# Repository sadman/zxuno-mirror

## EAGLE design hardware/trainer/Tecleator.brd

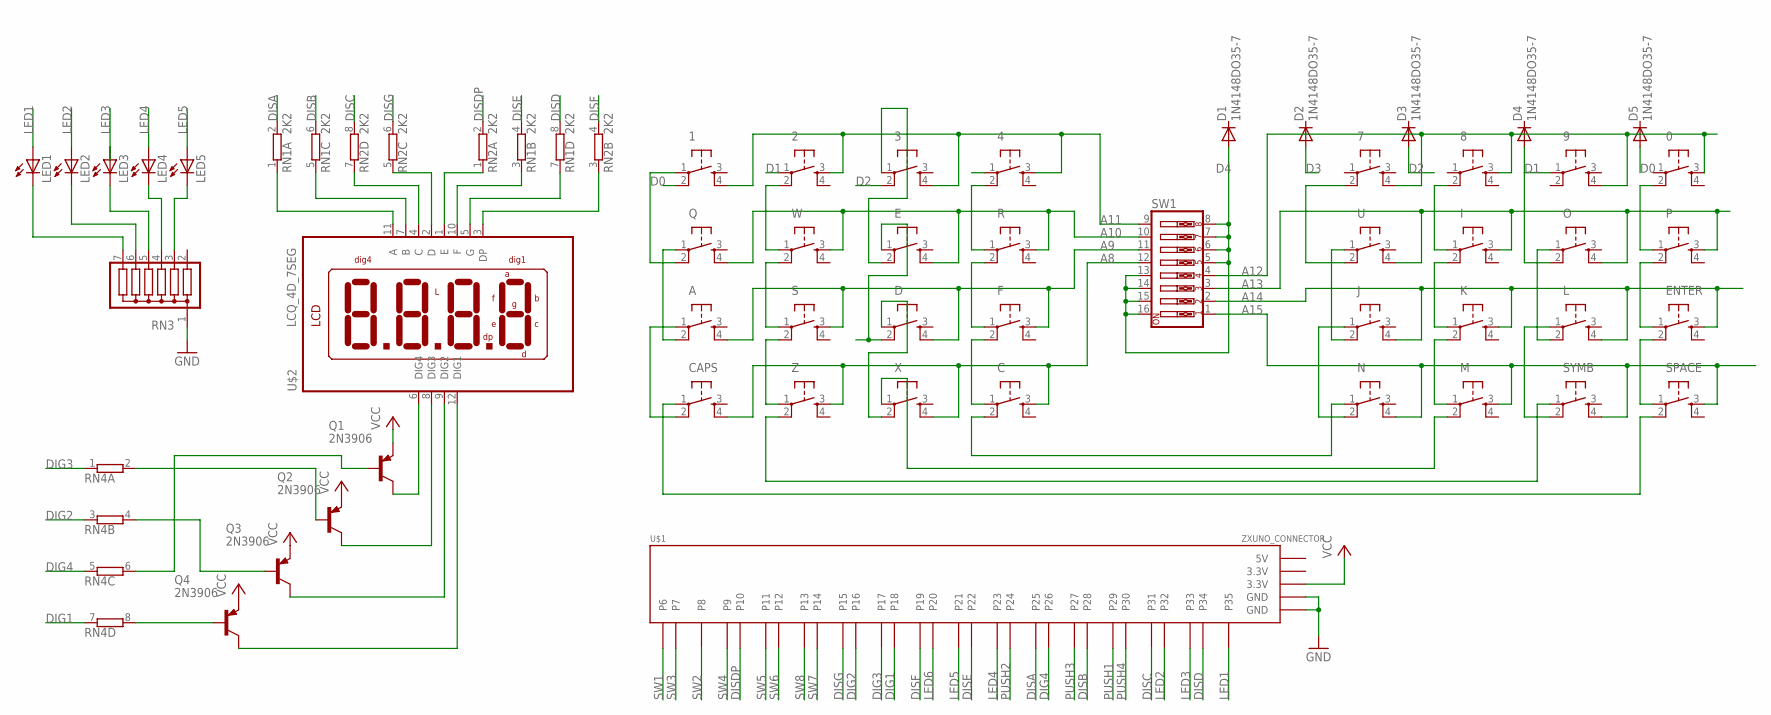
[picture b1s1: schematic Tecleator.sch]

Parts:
0, 1, 2, 3, 4, 7, 8, 9: DTS-6
A: DTS-6
C: DTS-6
CAPS: DTS-6
D: DTS-6
D1, D2, D3, D4, D5: 1N4148DO35-7; DO35-7
E: DTS-6
ENTER: DTS-6
F: DTS-6
I: DTS-6
J: DTS-6
K: DTS-6
L: DTS-6
LED1, LED2, LED3, LED4, LED5: LED3MM
M: DTS-6
N: DTS-6
O: DTS-6
P: DTS-6
Q: DTS-6
Q1, Q2, Q3, Q4: 2N3906; TO92
R: DTS-6
RN1, RN2: 2K2; SIL8
RN3: G06R; SIL7
RN4: E4R; SIL8
S: DTS-6
SPACE: DTS-6
SW1: SW_DIP-8; EDG-08
SYMB: DTS-6
U: DTS-6
U$1: ZXUNO_CONNECTOR
U$2: LCQ_4D_7SEG; LDQ_4D_7SEG
W: DTS-6
X: DTS-6
Z: DTS-6

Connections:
3.3V: U$1.3.3V@1 (3.3V)
5V: U$1.5V
A8: C.3, CAPS.4, SW1.12, X.4, Z.3
A9: A.4, D.4, F.3, S.3, SW1.11
A10: E.4, Q.4, R.3, SW1.10, W.3
A11: 1.4, 2.3, 3.4, 4.3, SW1.9
A12: 0.3, 7.4, 8.3, 9.4, SW1.4
A13: I.3, O.4, P.3, SW1.3, U.4
A14: ENTER.3, J.4, K.3, L.4, SW1.2
A15: M.3, N.4, SPACE.3, SW1.1, SYMB.4
D0: 1.2, D5.A
D1: 2.1, 9.1, D4.A, O.2
D2: 3.2, D3.A
D3: 4.1, D2.A
D4: D1.A, SW1.5, SW1.6, SW1.7, SW1.8, SW1.13, SW1.14, SW1.15, SW1.16
DIG1: RN4.7 (1), U$1.P18
DIG2: RN4.3 (1), U$1.P16
DIG3: RN4.1, U$1.P17
DIG4: RN4.5 (1), U$1.P26
DISA: RN1.2, U$1.P25
DISB: RN1.6 (2), U$1.P28
DISC: RN2.8 (2), U$1.P31
DISD: RN1.8 (2), U$1.P34
DISDP: RN2.2, U$1.P10
DISE: RN1.4 (2), U$1.P22
DISF: RN2.4 (2), U$1.P19
DISG: RN2.6 (2), U$1.P15
ELETE: M.2, X.1
GND: RN3.1, U$1.GND@1 (GND), U$1.GND@2 (GND)
LED1: LED1.A, U$1.P35
LED2: LED2.A, U$1.P32
LED3: LED3.A, U$1.P33
LED4: LED4.A, U$1.P23
LED5: LED5.A, U$1.P21
LED6: U$1.P20
unnamed: CAPS.1, SPACE.2
unnamed: 1.1, Q.2
unnamed: K.2, M.1
unnamed: Q1.1 (C), U$2.6 (DIG4)
unnamed: Q2.1 (C), U$2.8 (DIG3)
unnamed: Q3.1 (C), U$2.9 (DIG2)
unnamed: A.2, Q.1
unnamed: Q4.1 (C), U$2.12 (DIG1)
unnamed: A.1, CAPS.2
unnamed: 7.2, U.2
unnamed: 3.1, E.2
unnamed: S.1, W.2
unnamed: S.2, Z.1
unnamed: SYMB.1, Z.2
unnamed: Q4.2 (B), RN4.8 (2)
unnamed: RN1.1, U$2.11 (A)
unnamed: 4.2, R.1
unnamed: F.1, R.2
unnamed: C.1, F.2
unnamed: J.2, U.1
unnamed: J.1, N.2
unnamed: RN1.5 (1), U$2.7 (B)
unnamed: D.2, E.1
unnamed: 2.2, W.1
unnamed: RN2.7 (1), U$2.4 (C)
unnamed: RN2.5 (1), U$2.2 (D)
unnamed: RN2.1, U$2.1 (E)
unnamed: RN1.3 (1), U$2.10 (F)
unnamed: LED4.K (C), RN3.4
unnamed: LED5.K (C), RN3.3
unnamed: LED3.K (C), RN3.5
unnamed: LED2.K (C), RN3.6
unnamed: C.2, N.1
unnamed: L.1, SYMB.2
unnamed: LED1.K (C), RN3.7
unnamed: I.2, K.1
unnamed: 8.2, I.1
unnamed: L.2, O.1
unnamed: RN1.7 (1), U$2.5 (G)
unnamed: ENTER.2, SPACE.1
unnamed: ENTER.1, P.2
unnamed: 0.2, P.1
unnamed: RN2.3 (1), U$2.3 (DP)
unnamed: Q2.2 (B), RN4.2
unnamed: Q1.2 (B), RN4.6 (2)
unnamed: Q3.2 (B), RN4.4 (2)
unnamed: D.1, X.2
PUSH1: U$1.P29
PUSH2: U$1.P24
PUSH3: U$1.P27
PUSH4: U$1.P30
SW1: U$1.P6
SW2: U$1.P8
SW3: U$1.P7
SW4: U$1.P9
SW5: U$1.P11
SW6: U$1.P12
SW7: U$1.P14
SW8: U$1.P13
VCC: Q1.3 (E), Q2.3 (E), Q3.3 (E), Q4.3 (E), U$1.3.3V@2 (3.3V)

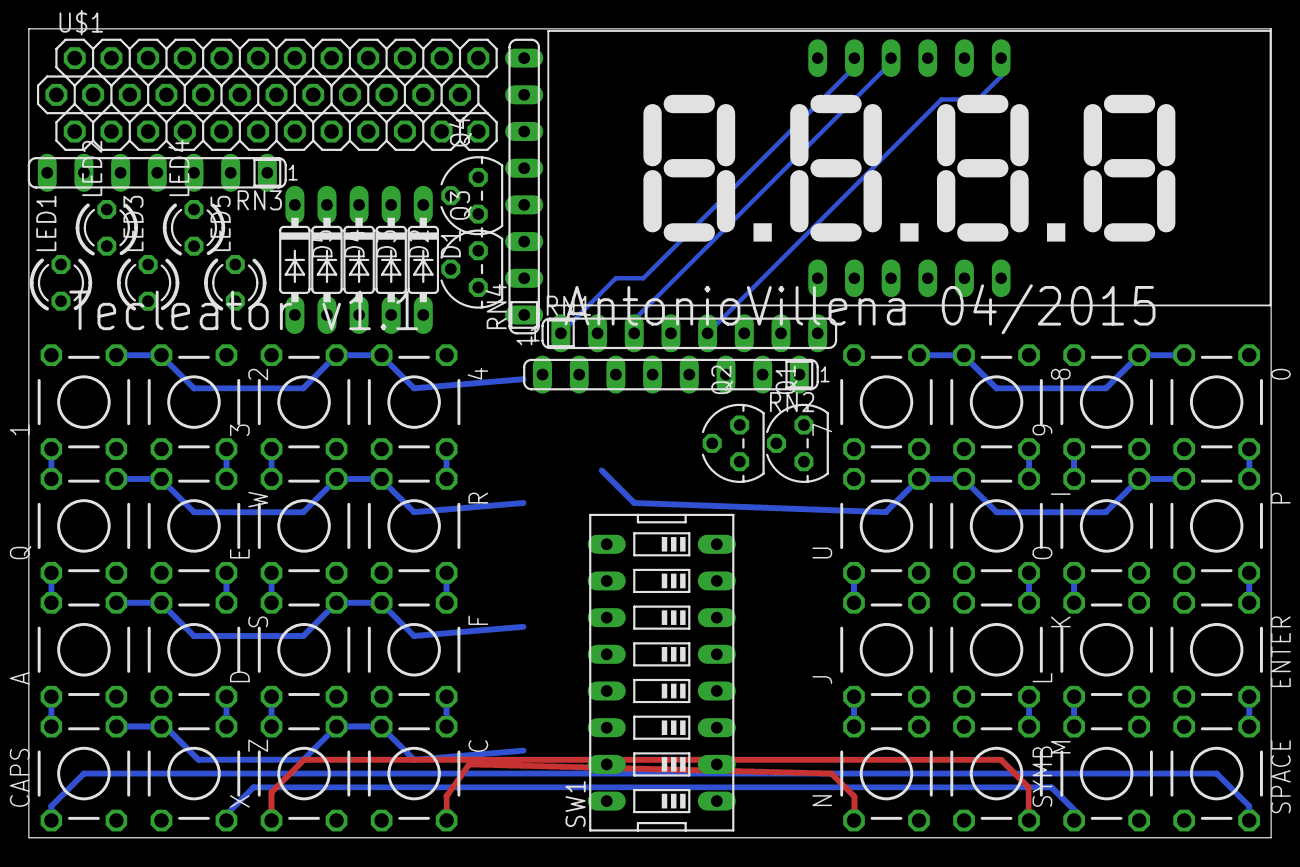
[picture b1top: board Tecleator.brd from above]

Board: 2 copper layers, 86.0 x 56.0 mm, 53 parts (0 on the bottom side), 80 nets.

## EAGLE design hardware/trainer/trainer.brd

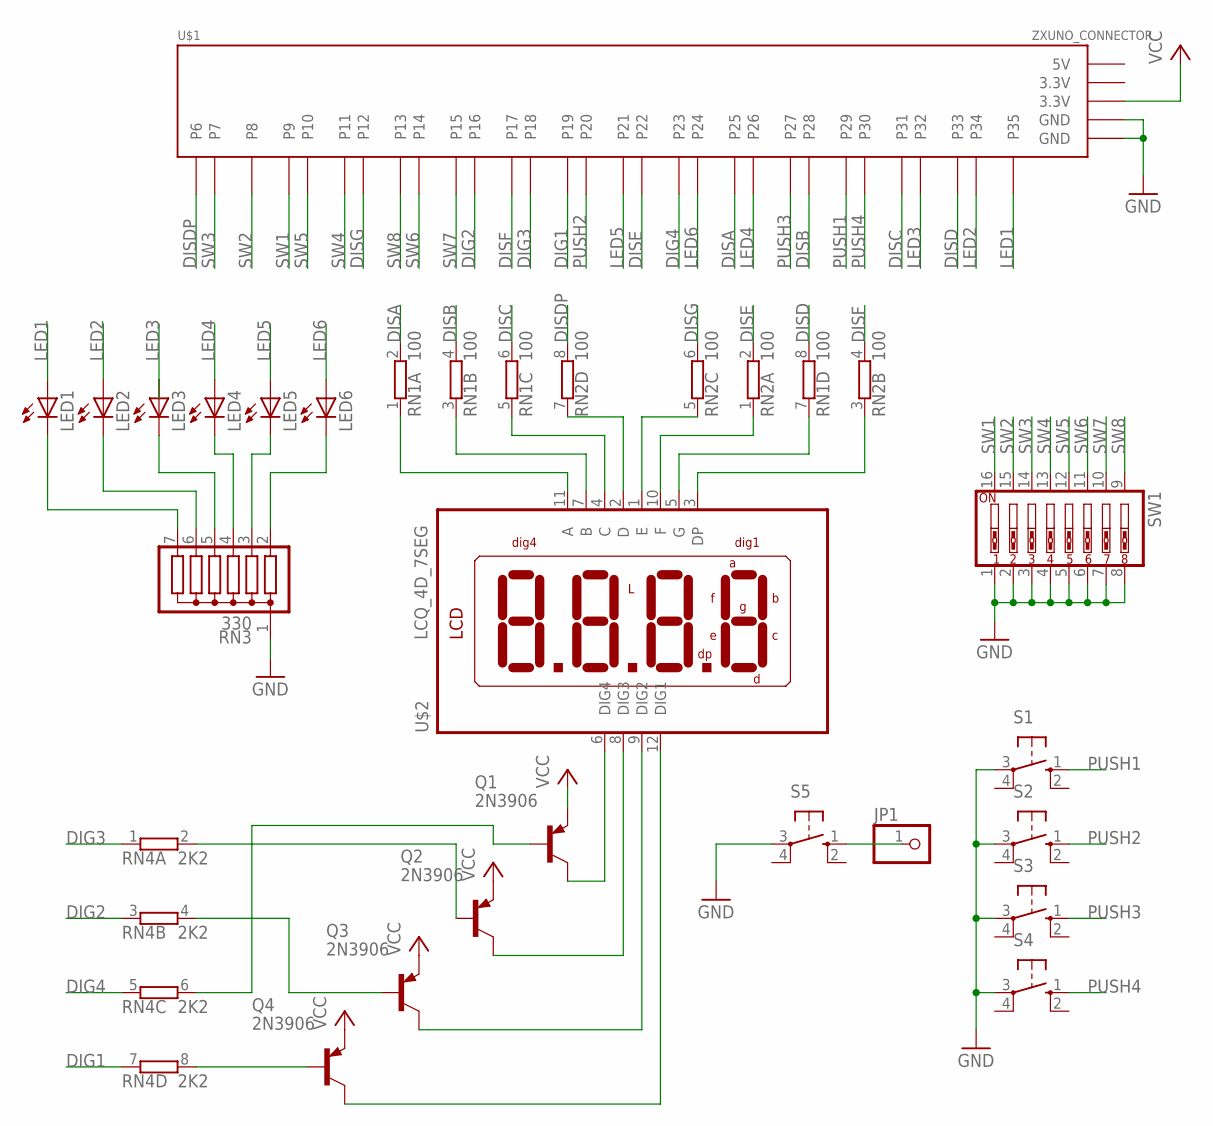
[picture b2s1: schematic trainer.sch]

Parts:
JP1: PINHD-1X1; 1X01
LED1, LED2, LED3, LED4, LED5, LED6: LED3MM
Q1, Q2, Q3, Q4: 2N3906; TO92
RN1, RN2: 100; SIL8
RN3: 330; SIL7
RN4: 2K2; SIL8
S1, S2, S3, S4, S5: 10-XX; B3F-10XX
SW1: SW_DIP-8; EDG-08
U$1: ZXUNO_CONNECTOR
U$2: LCQ_4D_7SEG; LDQ_4D_7SEG

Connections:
3.3V: U$1.3.3V@1 (3.3V)
5V: U$1.5V
DIG1: RN4.7 (1), U$1.P19
DIG2: RN4.3 (1), U$1.P16
DIG3: RN4.1, U$1.P18
DIG4: RN4.5 (1), U$1.P23
DISA: RN1.2, U$1.P25
DISB: RN1.4 (2), U$1.P28
DISC: RN1.6 (2), U$1.P31
DISD: RN1.8 (2), U$1.P33
DISDP: RN2.8 (2), U$1.P6
DISE: RN2.2, U$1.P22
DISF: RN2.4 (2), U$1.P17
DISG: RN2.6 (2), U$1.P12
GND: RN3.1, S1.3, S2.3, S3.3, S4.3, S5.3, SW1.1, SW1.2, SW1.3, SW1.4, SW1.5, SW1.6, SW1.7, SW1.8, U$1.GND@1 (GND), U$1.GND@2 (GND)
LED1: LED1.A, U$1.P35
LED2: LED2.A, U$1.P34
LED3: LED3.A, U$1.P32
LED4: LED4.A, U$1.P26
LED5: LED5.A, U$1.P21
LED6: LED6.A, U$1.P24
unnamed: Q1.1 (C), U$2.6 (DIG4)
unnamed: Q2.1 (C), U$2.8 (DIG3)
unnamed: Q3.1 (C), U$2.9 (DIG2)
unnamed: Q4.1 (C), U$2.12 (DIG1)
unnamed: Q2.2 (B), RN4.2
unnamed: Q1.2 (B), RN4.6 (2)
unnamed: Q3.2 (B), RN4.4 (2)
unnamed: Q4.2 (B), RN4.8 (2)
unnamed: RN1.1, U$2.11 (A)
unnamed: RN1.3 (1), U$2.7 (B)
unnamed: RN1.5 (1), U$2.4 (C)
unnamed: RN2.7 (1), U$2.2 (D)
unnamed: RN2.5 (1), U$2.1 (E)
unnamed: RN2.1, U$2.10 (F)
unnamed: JP1.1, S5.1 (S)
unnamed: RN2.3 (1), U$2.3 (DP)
unnamed: RN1.7 (1), U$2.5 (G)
unnamed: LED4.K (C), RN3.4
unnamed: LED5.K (C), RN3.3
unnamed: LED3.K (C), RN3.5
unnamed: LED2.K (C), RN3.6
unnamed: LED1.K (C), RN3.7
unnamed: LED6.K (C), RN3.2
PUSH1: S1.1 (S), U$1.P29
PUSH2: S2.1 (S), U$1.P20
PUSH3: S3.1 (S), U$1.P27
PUSH4: S4.1 (S), U$1.P30
SW1: SW1.16, U$1.P9
SW2: SW1.15, U$1.P8
SW3: SW1.14, U$1.P7
SW4: SW1.13, U$1.P11
SW5: SW1.12, U$1.P10
SW6: SW1.11, U$1.P14
SW7: SW1.10, U$1.P15
SW8: SW1.9, U$1.P13
VCC: Q1.3 (E), Q2.3 (E), Q3.3 (E), Q4.3 (E), U$1.3.3V@2 (3.3V)

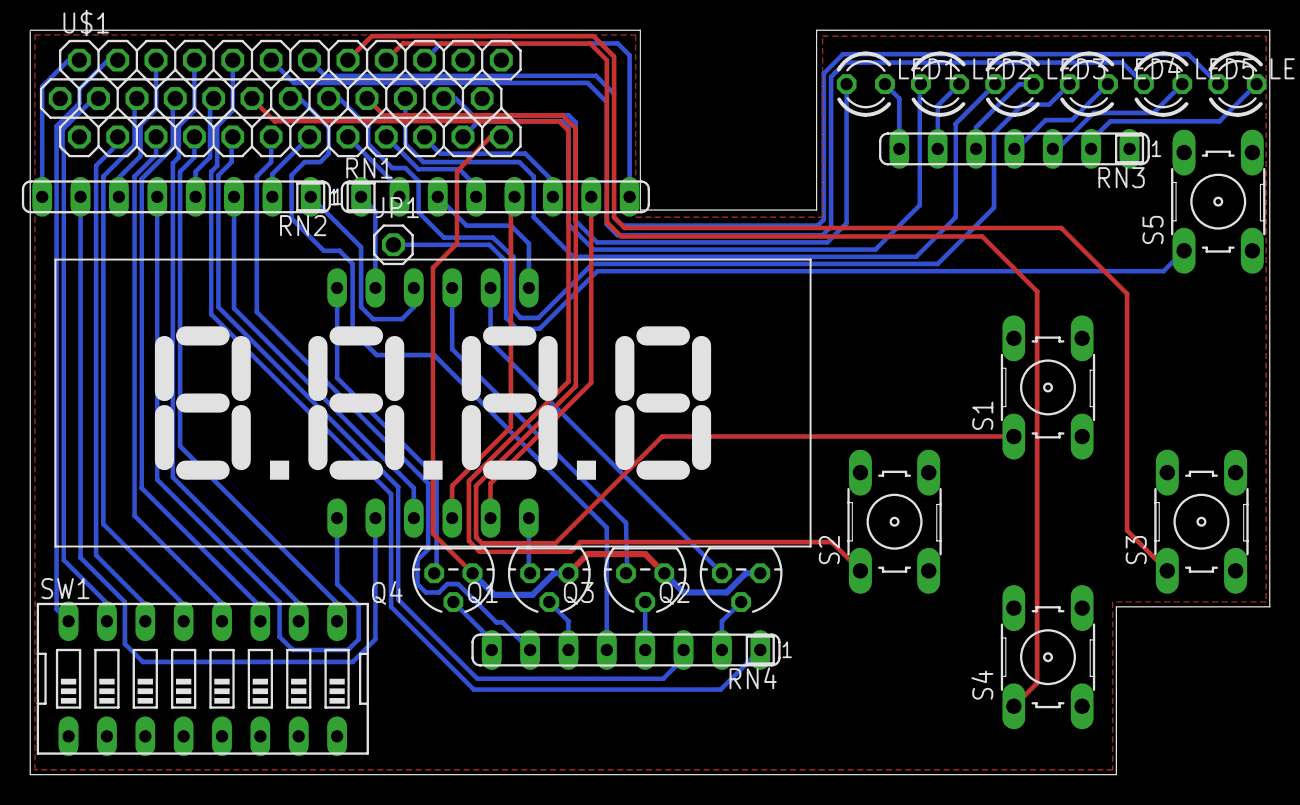
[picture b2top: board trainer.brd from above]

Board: 2 copper layers, 82.1 x 49.3 mm, 23 parts (0 on the bottom side), 55 nets.

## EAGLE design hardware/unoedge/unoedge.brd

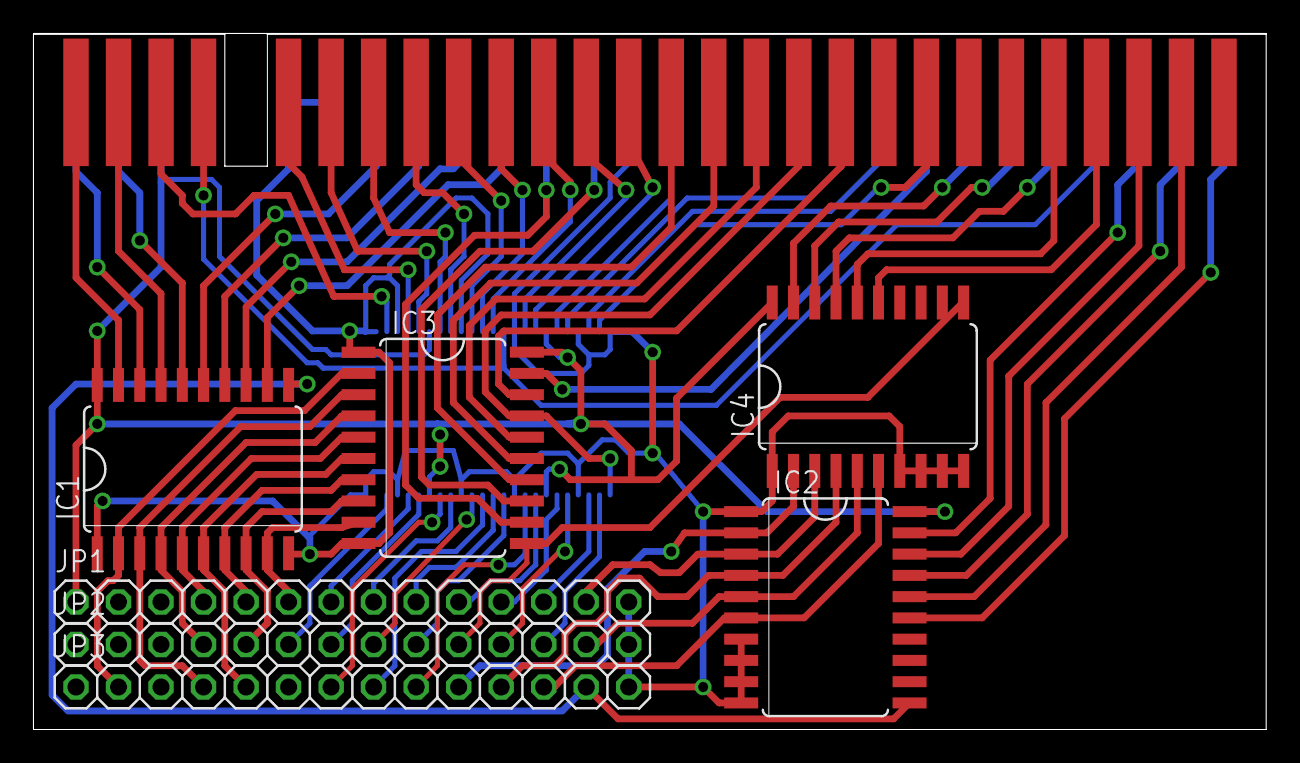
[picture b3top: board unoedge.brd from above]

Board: 2 copper layers, 73.7 x 41.6 mm, 9 parts (1 on the bottom side), 73 nets.

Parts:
IC1, IC2, IC3, IC4: 74HC574D; SO20W
IC5: 74AC16245; SSOP48DL
JP1: fila1; 1X14
JP2: fila2; 1X14
JP3: fila3; 1X14
U$2: CONECTOR_EDGE_LADO_SPECTRUM; CONECTOR_LADO_SPECTRUM

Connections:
/BUSAK: IC2.19, U$2.P$52
/BUSRQ: IC5.44, U$2.P$45
/HALT: IC3.14, U$2.P$14
/INT: IC5.40, U$2.P$12
/IORQ: IC3.16, U$2.P$16
/IORQULA: IC3.13, U$2.P$39
/M1: IC4.16, U$2.P$23
/MREQ: IC3.15, U$2.P$15
/NMI: IC5.41, U$2.P$13
/RD: IC3.17, IC5.1, U$2.P$17
/RESET: IC5.46, U$2.P$46
/RFSH: IC4.15, U$2.P$24
/WAIT: IC5.47, U$2.P$20
/WR: IC3.18, U$2.P$18
A0: IC1.14, U$2.P$35
A1: IC1.13, U$2.P$36
A2: IC1.12, U$2.P$37
A3: IC3.12, U$2.P$38
A4: IC4.17, U$2.P$50
A5: IC4.18, U$2.P$49
A6: IC4.19, U$2.P$48
A7: IC3.19, U$2.P$47
A8: IC2.18, U$2.P$25
A9: IC2.17, U$2.P$53
A10: IC2.16, U$2.P$26
A11: IC2.15, U$2.P$54
A12: IC1.16, U$2.P$29
A13: IC1.17, U$2.P$2
A14: IC1.18, U$2.P$28
A15: IC1.19, U$2.P$1
CKEXT: IC1.15, U$2.P$34
D0: IC5.29, U$2.P$5
D1: IC5.30, U$2.P$6
D2: IC5.32, U$2.P$7
D3: IC5.36, U$2.P$10
D4: IC5.37, U$2.P$11
D5: IC5.35, U$2.P$9
D6: IC5.33, U$2.P$8
D7: IC5.27, U$2.P$3
EXT3: IC1.2, IC3.2, JP3.2
EXT7: IC1.5, IC3.5, JP1.4
EXT8: IC1.4, IC3.4, JP2.4
EXT9: IC1.3, IC3.3, JP3.4
EXT10: IC1.7, IC3.7, JP1.5
EXT11: IC1.8, IC3.8, JP2.5
EXT12: IC1.6, IC3.6, JP3.5
EXT13: IC1.9, IC3.9, JP1.6
EXT14: IC5.22, JP2.6
EXT16: IC5.20, JP1.7
EXT17: IC5.19, JP2.7
EXT18: IC5.17, JP3.7
EXT19: IC5.16, JP1.8
EXT20: IC5.14, JP2.8
EXT21: IC5.13, JP3.8
EXT22: IC5.12, JP1.9
EXT23: IC5.11, JP2.9
EXT24: IC5.9, JP3.9
EXT25: IC5.8, JP1.10
EXT26: IC3.11, IC4.11, JP2.10
EXT27: IC2.2, IC4.2, JP3.10
EXT28: IC5.6, JP1.11
EXT29: IC5.5, JP2.11
EXT30: IC2.4, IC4.4, JP3.11
EXT31: IC5.3, JP1.12
EXT32: IC5.2, JP2.12
EXT33: IC2.6, IC4.6, JP3.12
EXT34: IC2.3, IC4.3, JP1.13
EXT35: IC2.5, IC4.5, JP2.13
EXT36: IC1.11, IC2.11, JP3.13
GND: IC1.1, IC1.10, IC2.1, IC2.7, IC2.8, IC2.9, IC2.10, IC3.1, IC3.10, IC4.1, IC4.7, IC4.8, IC4.9, IC4.10, IC5.4, IC5.10, IC5.15, IC5.21, IC5.24, IC5.25, IC5.26, IC5.28, IC5.34, IC5.39, IC5.45, IC5.48, JP1.14, JP2.14, JP3.14, U$2.P$32, U$2.P$33, U$2.P$40
ROM1: IC5.38, U$2.P$4, U$2.P$51
ROM2: IC5.43, U$2.P$41
VCC: IC1.20, IC2.20, IC3.20, IC4.20, IC5.7, IC5.18, IC5.31, IC5.42, JP1.1, U$2.P$30

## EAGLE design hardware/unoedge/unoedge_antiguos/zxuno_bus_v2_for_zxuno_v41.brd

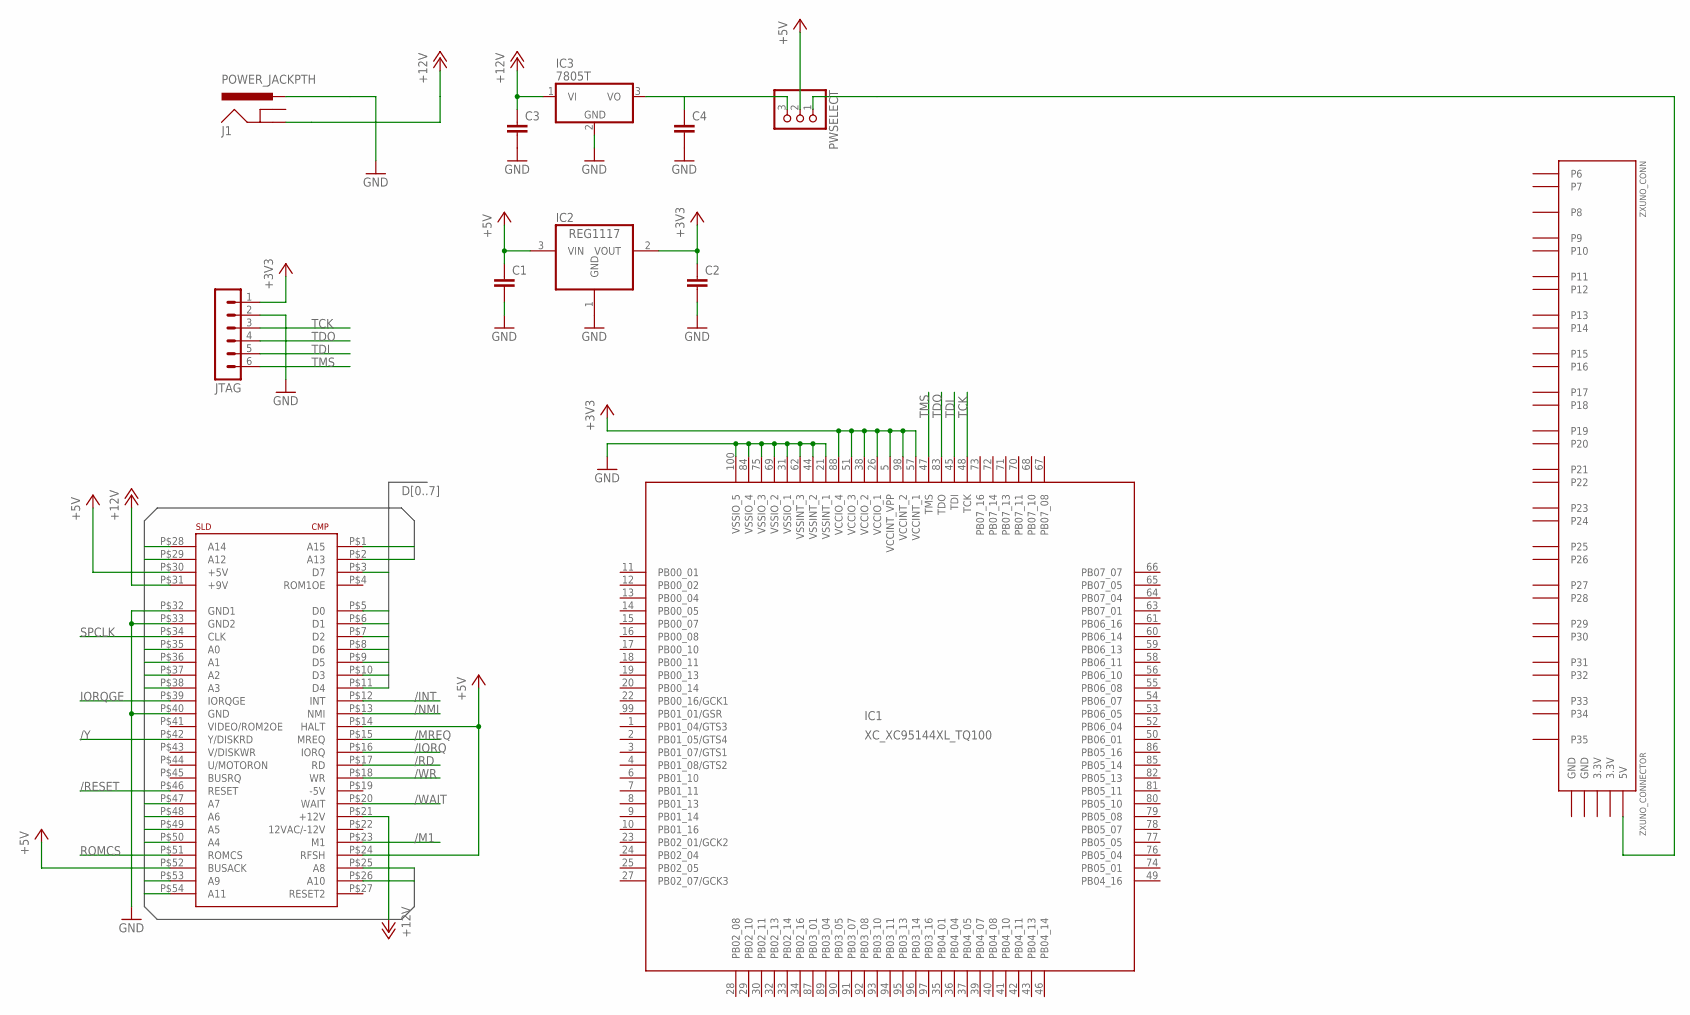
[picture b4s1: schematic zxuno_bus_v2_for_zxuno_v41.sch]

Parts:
C1, C2, C3, C4: C-EUC1206K; C1206K
IC1: XC_XC95144XL_TQ100; XC_XC-TQ100
IC2: REG1117; SOT223
IC3: 7805T; TO220H
J1: POWER_JACKPTH; POWER_JACK_PTH
JTAG: MA06-1
PWSELECT: PINHD-1X3; 1X03
U$1: CONECTOR_EDGE_LADO_SPECTRUM; CONECTOR_LADO_SPECTRUM
ZXUNO_CONN: ZXUNO_CONNECTOR

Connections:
3.3V: ZXUNO_CONN.3.3V@1 (3.3V), ZXUNO_CONN.3.3V@2 (3.3V)
+3V3: C2.1, IC1.5 (VCCINT_VPP), IC1.26 (VCCIO_1), IC1.38 (VCCIO_2), IC1.51 (VCCIO_3), IC1.57 (VCCINT_1), IC1.88 (VCCIO_4), IC1.98 (VCCINT_2), IC2.2 (VOUT), JTAG.1
+5V: C1.1, IC2.3 (VIN), PWSELECT.2, U$1.P$14 (HALT), U$1.P$24 (RFSH), U$1.P$30 (+5V), U$1.P$52 (BUSACK)
+12V: C3.1, IC3.1 (VI), J1.GND, U$1.P$21 (+12V), U$1.P$31 (+9V)
/INT: U$1.P$12 (INT)
/IORQ: U$1.P$16 (IORQ)
/M1: U$1.P$23 (M1)
/MREQ: U$1.P$15 (MREQ)
/NMI: U$1.P$13 (NMI)
/RD: U$1.P$17 (RD)
/RESET: U$1.P$46 (RESET)
/WAIT: U$1.P$20 (WAIT)
/WR: U$1.P$18 (WR)
/Y: U$1.P$42 (Y/DISKRD)
A0: U$1.P$35 (A0)
A1: U$1.P$36 (A1)
A2: U$1.P$37 (A2)
A3: U$1.P$38 (A3)
A4: U$1.P$50 (A4)
A5: U$1.P$49 (A5)
A6: U$1.P$48 (A6)
A7: U$1.P$47 (A7)
A8: U$1.P$25 (A8)
A9: U$1.P$53 (A9)
A10: U$1.P$26 (A10)
A11: U$1.P$54 (A11)
A12: U$1.P$29 (A12)
A13: U$1.P$2 (A13)
A14: U$1.P$28 (A14)
A15: U$1.P$1 (A15)
D0: U$1.P$5 (D0)
D1: U$1.P$6 (D1)
D2: U$1.P$7 (D2)
D3: U$1.P$10 (D3)
D4: U$1.P$11 (D4)
D5: U$1.P$9 (D5)
D6: U$1.P$8 (D6)
D7: U$1.P$3 (D7)
GND: C1.2, C2.2, C3.2, C4.2, IC1.21 (VSSINT_1), IC1.31 (VSSIO_1), IC1.44 (VSSINT_2), IC1.62 (VSSINT_3), IC1.69 (VSSIO_2), IC1.75 (VSSIO_3), IC1.84 (VSSIO_4), IC1.100 (VSSIO_5), IC2.1 (GND), IC3.2 (GND), J1.PWR, JTAG.2, U$1.P$32 (GND1), U$1.P$33 (GND2), U$1.P$40 (GND), ZXUNO_CONN.GND@1 (GND), ZXUNO_CONN.GND@2 (GND)
IORQGE: U$1.P$39 (IORQGE)
unnamed: PWSELECT.1, ZXUNO_CONN.5V
unnamed: C4.1, IC3.3 (VO), PWSELECT.3
ROMCS: U$1.P$51 (ROMCS)
SPCLK: U$1.P$34 (CLK)
TCK: IC1.48 (TCK), JTAG.3
TDI: IC1.45 (TDI), JTAG.5
TDO: IC1.83 (TDO), JTAG.4
TMS: IC1.47 (TMS), JTAG.6

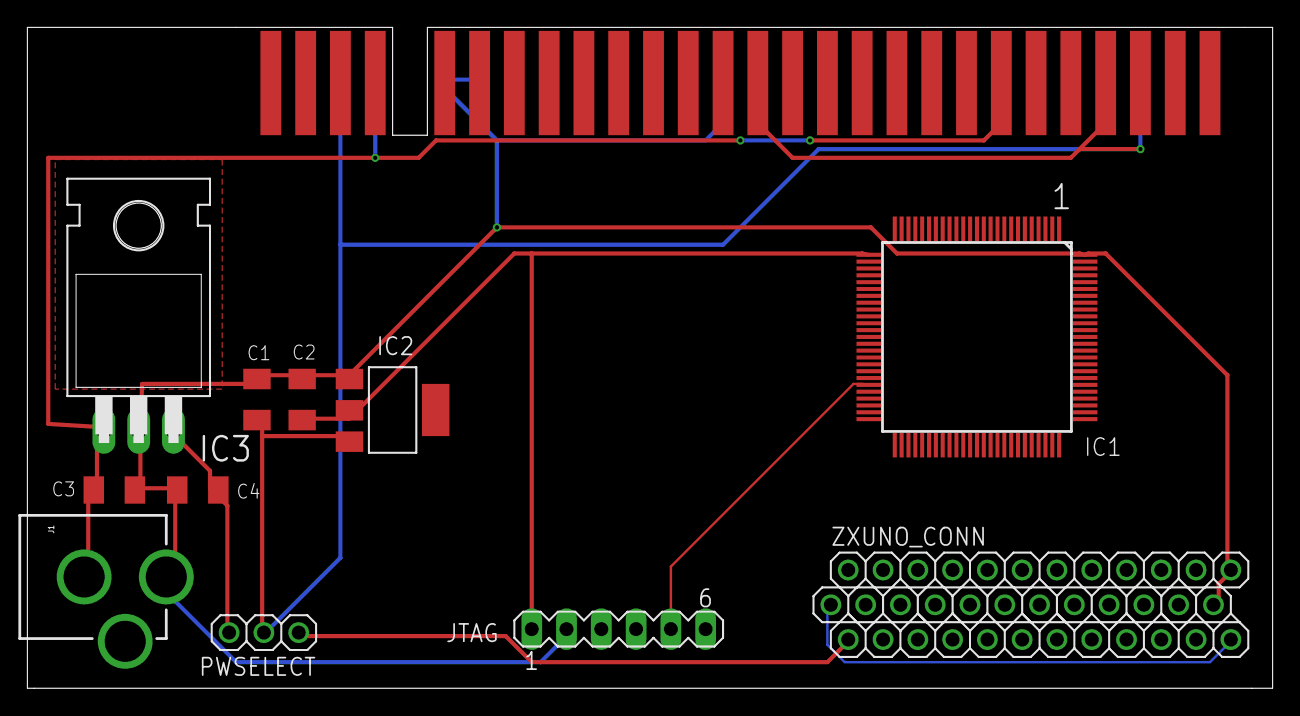
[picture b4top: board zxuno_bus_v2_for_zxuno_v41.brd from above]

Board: 2 copper layers, 90.9 x 48.3 mm, 12 parts (0 on the bottom side), 11 nets.

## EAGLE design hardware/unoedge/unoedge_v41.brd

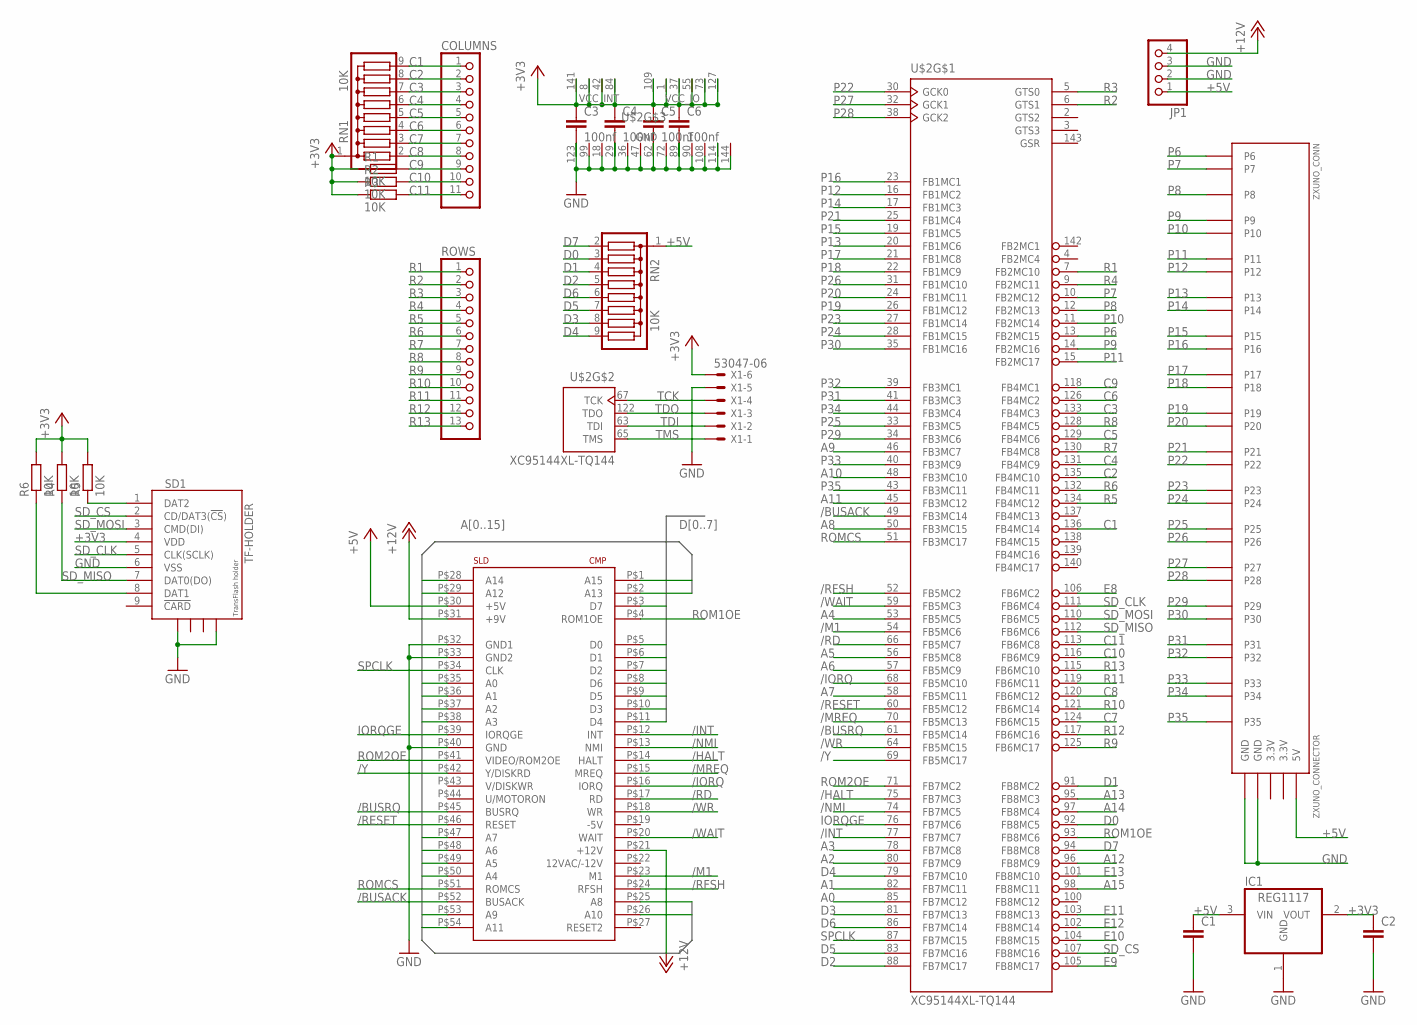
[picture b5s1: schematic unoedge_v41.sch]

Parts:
C1, C2: C-EUC0805; C0805
C3, C4, C5, C6: 100nf; C0603
COLUMNS: PINHD-1X11; 1X11
IC1: REG1117; SOT223
JP1: PINHD-1X4; 1X04
R1, R2, R3, R4, R5, R6: 10K; R0603
RN1, RN2: 10K; SIL9
ROWS: PINHD-1X13; 1X13
SD1: TF-HOLDER; TF-PULL
U$1: CONECTOR_EDGE_LADO_SPECTRUM; CONECTOR_LADO_SPECTRUM
U$2: XC95144XL-TQ144; TQ144
X1: 53047-06
ZXUNO_CONN: ZXUNO_CONNECTOR

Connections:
3.3V: ZXUNO_CONN.3.3V@1 (3.3V), ZXUNO_CONN.3.3V@2 (3.3V)
+3V3: C2.1, C3.1, C4.1, C5.1, C6.1, IC1.2 (VOUT), R1.1, R2.1, R3.1, R4.2, R5.2, R6.2, RN1.1, SD1.4 (VDD), U$2.1 (VCC_IO), U$2.8 (VCC_INT), U$2.37 (VCC_IO), U$2.42 (VCC_INT), U$2.55 (VCC_IO), U$2.73 (VCC_IO), U$2.84 (VCC_INT), U$2.109 (VCC_IO), U$2.127 (VCC_IO), U$2.141 (VCC_INT), X1.1
+5V: C1.1, IC1.3 (VIN), JP1.1, RN2.1, U$1.P$30 (+5V), ZXUNO_CONN.5V
+12V: JP1.4, U$1.P$21 (+12V), U$1.P$31 (+9V)
/BUSACK: U$1.P$52 (BUSACK), U$2.49 (FB3MC14)
/BUSRQ: U$1.P$45 (BUSRQ), U$2.61 (FB5MC14)
/HALT: U$1.P$14 (HALT), U$2.75 (FB7MC3)
/INT: U$1.P$12 (INT), U$2.77 (FB7MC7)
/IORQ: U$1.P$16 (IORQ), U$2.68 (FB5MC10)
/M1: U$1.P$23 (M1), U$2.54 (FB5MC6)
/MREQ: U$1.P$15 (MREQ), U$2.70 (FB5MC13)
/NMI: U$1.P$13 (NMI), U$2.74 (FB7MC5)
/RD: U$1.P$17 (RD), U$2.66 (FB5MC7)
/RESET: U$1.P$46 (RESET), U$2.60 (FB5MC12)
/RFSH: U$1.P$24 (RFSH), U$2.52 (FB5MC2)
/WAIT: U$1.P$20 (WAIT), U$2.59 (FB5MC3)
/WR: U$1.P$18 (WR), U$2.64 (FB5MC15)
/Y: U$1.P$42 (Y/DISKRD), U$2.69 (FB5MC17)
A0: U$1.P$35 (A0), U$2.85 (FB7MC12)
A1: U$1.P$36 (A1), U$2.82 (FB7MC11)
A2: U$1.P$37 (A2), U$2.80 (FB7MC9)
A3: U$1.P$38 (A3), U$2.78 (FB7MC8)
A4: U$1.P$50 (A4), U$2.53 (FB5MC5)
A5: U$1.P$49 (A5), U$2.56 (FB5MC8)
A6: U$1.P$48 (A6), U$2.57 (FB5MC9)
A7: U$1.P$47 (A7), U$2.58 (FB5MC11)
A8: U$1.P$25 (A8), U$2.50 (FB3MC15)
A9: U$1.P$53 (A9), U$2.46 (FB3MC7)
A10: U$1.P$26 (A10), U$2.48 (FB3MC10)
A11: U$1.P$54 (A11), U$2.45 (FB3MC12)
A12: U$1.P$29 (A12), U$2.96 (FB8MC9)
A13: U$1.P$2 (A13), U$2.95 (FB8MC3)
A14: U$1.P$28 (A14), U$2.97 (FB8MC4)
A15: U$1.P$1 (A15), U$2.98 (FB8MC11)
C1: COLUMNS.1, RN1.9, U$2.136 (FB4MC14)
C2: COLUMNS.2, RN1.8, U$2.135 (FB4MC10)
C3: COLUMNS.3, RN1.7, U$2.133 (FB4MC3)
C4: COLUMNS.4, RN1.6, U$2.131 (FB4MC9)
C5: COLUMNS.5, RN1.5, U$2.129 (FB4MC6)
C6: COLUMNS.6, RN1.4, U$2.126 (FB4MC2)
C7: COLUMNS.7, RN1.3, U$2.124 (FB6MC15)
C8: COLUMNS.8, RN1.2, U$2.120 (FB6MC12)
C9: COLUMNS.9, R1.2, U$2.118 (FB4MC1)
C10: COLUMNS.10, R2.2, U$2.116 (FB6MC9)
C11: COLUMNS.11, R3.2, U$2.113 (FB6MC8)
D0: RN2.3, U$1.P$5 (D0), U$2.92 (FB8MC5)
D1: RN2.4, U$1.P$6 (D1), U$2.91 (FB8MC2)
D2: RN2.5, U$1.P$7 (D2), U$2.88 (FB7MC17)
D3: RN2.8, U$1.P$10 (D3), U$2.81 (FB7MC13)
D4: RN2.9, U$1.P$11 (D4), U$2.79 (FB7MC10)
D5: RN2.7, U$1.P$9 (D5), U$2.83 (FB7MC16)
D6: RN2.6, U$1.P$8 (D6), U$2.86 (FB7MC14)
D7: RN2.2, U$1.P$3 (D7), U$2.94 (FB8MC8)
E8: U$2.106 (FB6MC2)
E9: U$2.105 (FB8MC17)
E10: U$2.104 (FB8MC15)
E11: U$2.103 (FB8MC13)
E12: U$2.102 (FB8MC14)
E13: U$2.101 (FB8MC10)
GND: C1.2, C2.2, C3.2, C4.2, C5.2, C6.2, IC1.1 (GND), JP1.2, JP1.3, SD1.6 (VSS), SD1.S1, SD1.S4, U$1.P$32 (GND1), U$1.P$33 (GND2), U$1.P$40 (GND), U$2.18 (GND), U$2.29 (GND), U$2.36 (GND), U$2.47 (GND), U$2.62 (GND), U$2.72 (GND), U$2.89 (GND), U$2.90 (GND), U$2.99 (GND), U$2.108 (GND), U$2.114 (GND), U$2.123 (GND), U$2.144 (GND), X1.2, ZXUNO_CONN.GND@1 (GND), ZXUNO_CONN.GND@2 (GND)
IORQGE: U$1.P$39 (IORQGE), U$2.76 (FB7MC6)
unnamed: R6.1, SD1.8 (DAT1)
unnamed: R5.1, SD1.1 (DAT2)
P6: U$2.13 (FB2MC15), ZXUNO_CONN.P6
P7: U$2.10 (FB2MC12), ZXUNO_CONN.P7
P8: U$2.12 (FB2MC13), ZXUNO_CONN.P8
P9: U$2.14 (FB2MC16), ZXUNO_CONN.P9
P10: U$2.11 (FB2MC14), ZXUNO_CONN.P10
P11: U$2.15 (FB2MC17), ZXUNO_CONN.P11
P12: U$2.16 (FB1MC2), ZXUNO_CONN.P12
P13: U$2.20 (FB1MC6), ZXUNO_CONN.P13
P14: U$2.17 (FB1MC3), ZXUNO_CONN.P14
P15: U$2.19 (FB1MC5), ZXUNO_CONN.P15
P16: U$2.23 (FB1MC1), ZXUNO_CONN.P16
P17: U$2.21 (FB1MC8), ZXUNO_CONN.P17
P18: U$2.22 (FB1MC9), ZXUNO_CONN.P18
P19: U$2.26 (FB1MC12), ZXUNO_CONN.P19
P20: U$2.24 (FB1MC11), ZXUNO_CONN.P20
P21: U$2.25 (FB1MC4), ZXUNO_CONN.P21
P22: U$2.30 (GCK0), ZXUNO_CONN.P22
P23: U$2.27 (FB1MC14), ZXUNO_CONN.P23
P24: U$2.28 (FB1MC15), ZXUNO_CONN.P24
P25: U$2.33 (FB3MC5), ZXUNO_CONN.P25
P26: U$2.31 (FB1MC10), ZXUNO_CONN.P26
P27: U$2.32 (GCK1), ZXUNO_CONN.P27
P28: U$2.38 (GCK2), ZXUNO_CONN.P28
P29: U$2.34 (FB3MC6), ZXUNO_CONN.P29
P30: U$2.35 (FB1MC16), ZXUNO_CONN.P30
P31: U$2.41 (FB3MC3), ZXUNO_CONN.P31
P32: U$2.39 (FB3MC1), ZXUNO_CONN.P32
P33: U$2.40 (FB3MC9), ZXUNO_CONN.P33
P34: U$2.44 (FB3MC4), ZXUNO_CONN.P34
P35: U$2.43 (FB3MC11), ZXUNO_CONN.P35
R1: ROWS.1, U$2.7 (FB2MC10)
R2: ROWS.2, U$2.6 (GTS1)
R3: ROWS.3, U$2.5 (GTS0)
R4: ROWS.4, U$2.9 (FB2MC11)
R5: ROWS.5, U$2.134 (FB4MC12)
R6: ROWS.6, U$2.132 (FB4MC11)
R7: ROWS.7, U$2.130 (FB4MC8)
R8: ROWS.8, U$2.128 (FB4MC5)
R9: ROWS.9, U$2.125 (FB6MC17)
R10: ROWS.10, U$2.121 (FB6MC14)
R11: ROWS.11, U$2.119 (FB6MC11)
R12: ROWS.12, U$2.117 (FB6MC16)
R13: ROWS.13, U$2.115 (FB6MC10)
ROM1OE: U$1.P$4 (ROM1OE), U$2.93 (FB8MC6)
ROM2OE: U$1.P$41 (VIDEO/ROM2OE), U$2.71 (FB7MC2)
ROMCS: U$1.P$51 (ROMCS), U$2.51 (FB3MC17)
SD_CLK: SD1.5 (CLK(SCLK)), U$2.111 (FB6MC4)
SD_CS: SD1.2 (CD/DAT3(!CS!)), U$2.107 (FB8MC16)
SD_MISO: R4.1, SD1.7 (DAT0(DO)), U$2.112 (FB6MC6)
SD_MOSI: SD1.3 (CMD(DI)), U$2.110 (FB6MC5)
SPCLK: U$1.P$34 (CLK), U$2.87 (FB7MC15)
TCK: U$2.67 (TCK), X1.3
TDI: U$2.63 (TDI), X1.5
TDO: U$2.122 (TDO), X1.4
TMS: U$2.65 (TMS), X1.6

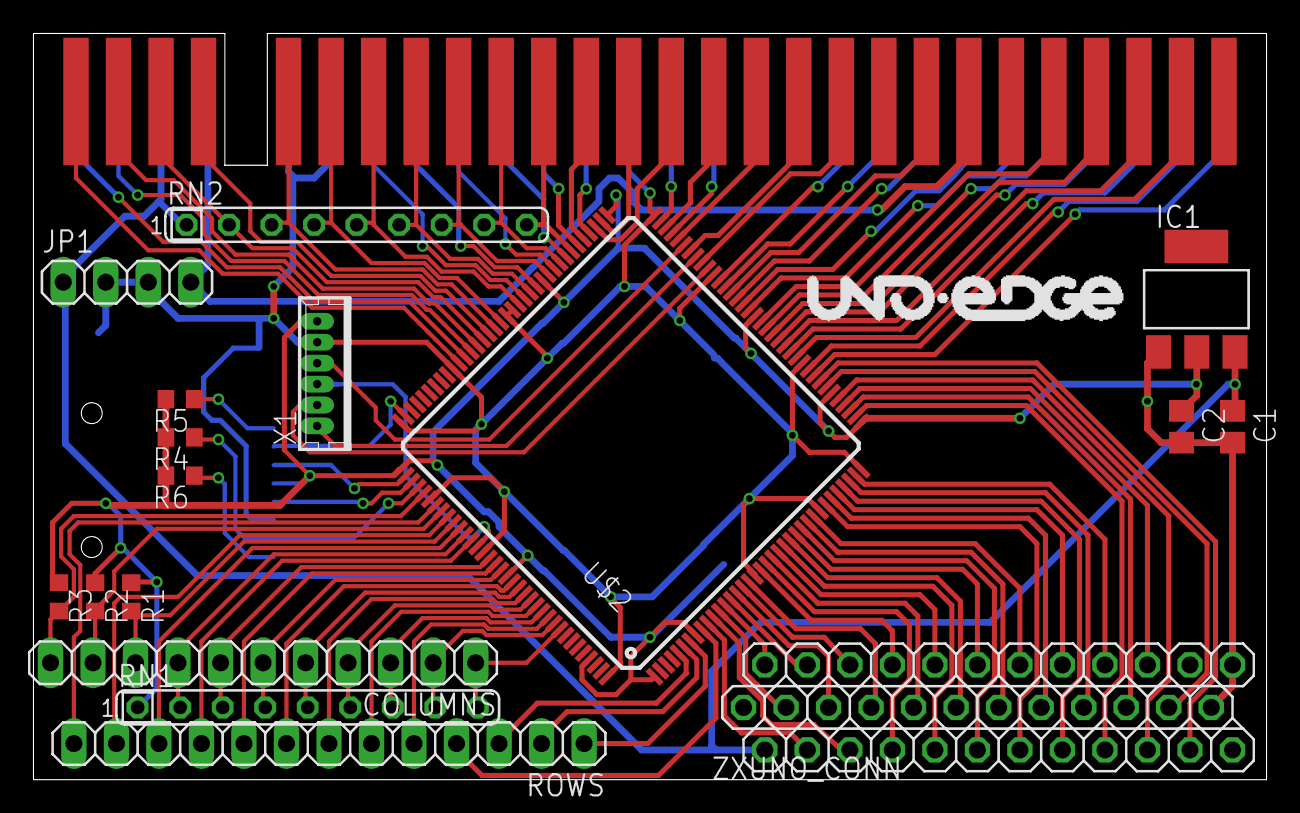
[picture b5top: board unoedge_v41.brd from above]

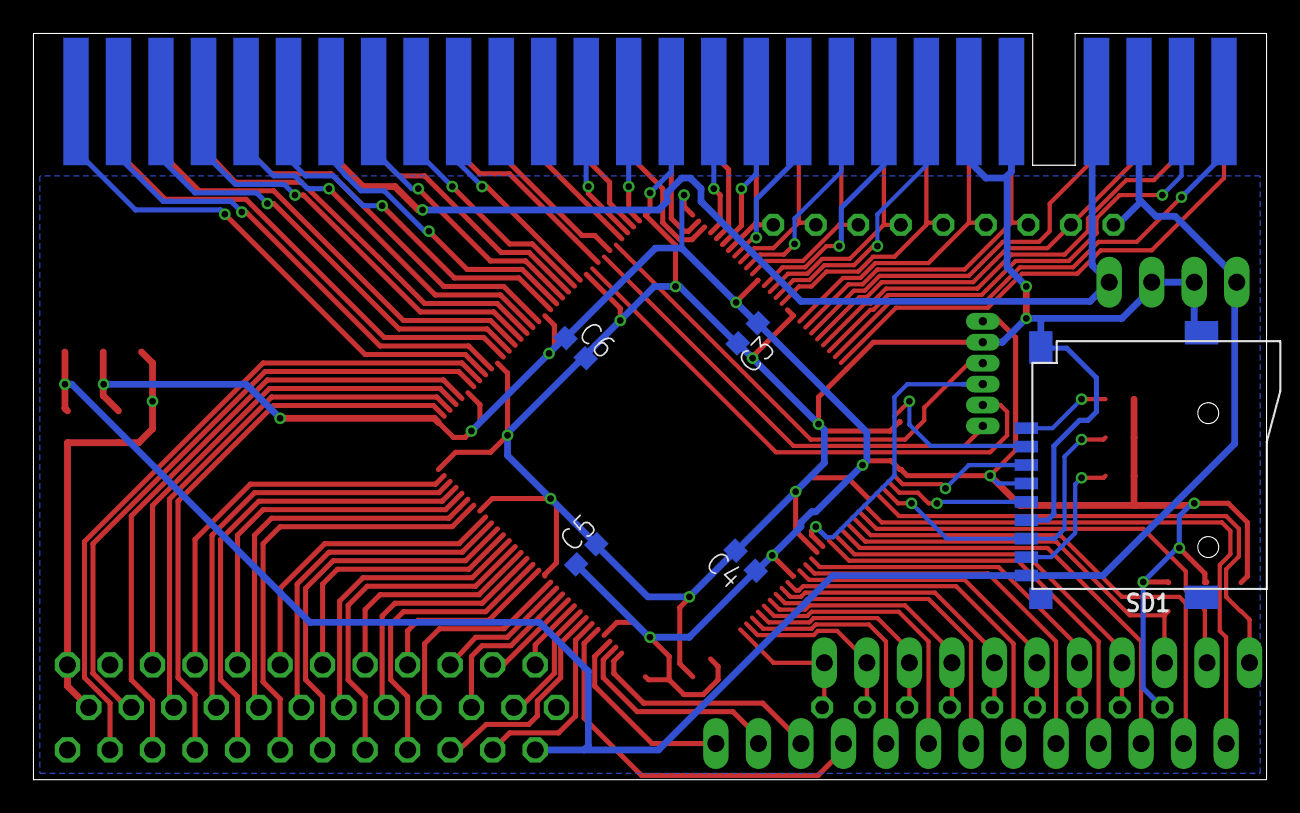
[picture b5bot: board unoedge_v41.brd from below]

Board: 2 copper layers, 73.7 x 44.6 mm, 23 parts (5 on the bottom side), 112 nets.
